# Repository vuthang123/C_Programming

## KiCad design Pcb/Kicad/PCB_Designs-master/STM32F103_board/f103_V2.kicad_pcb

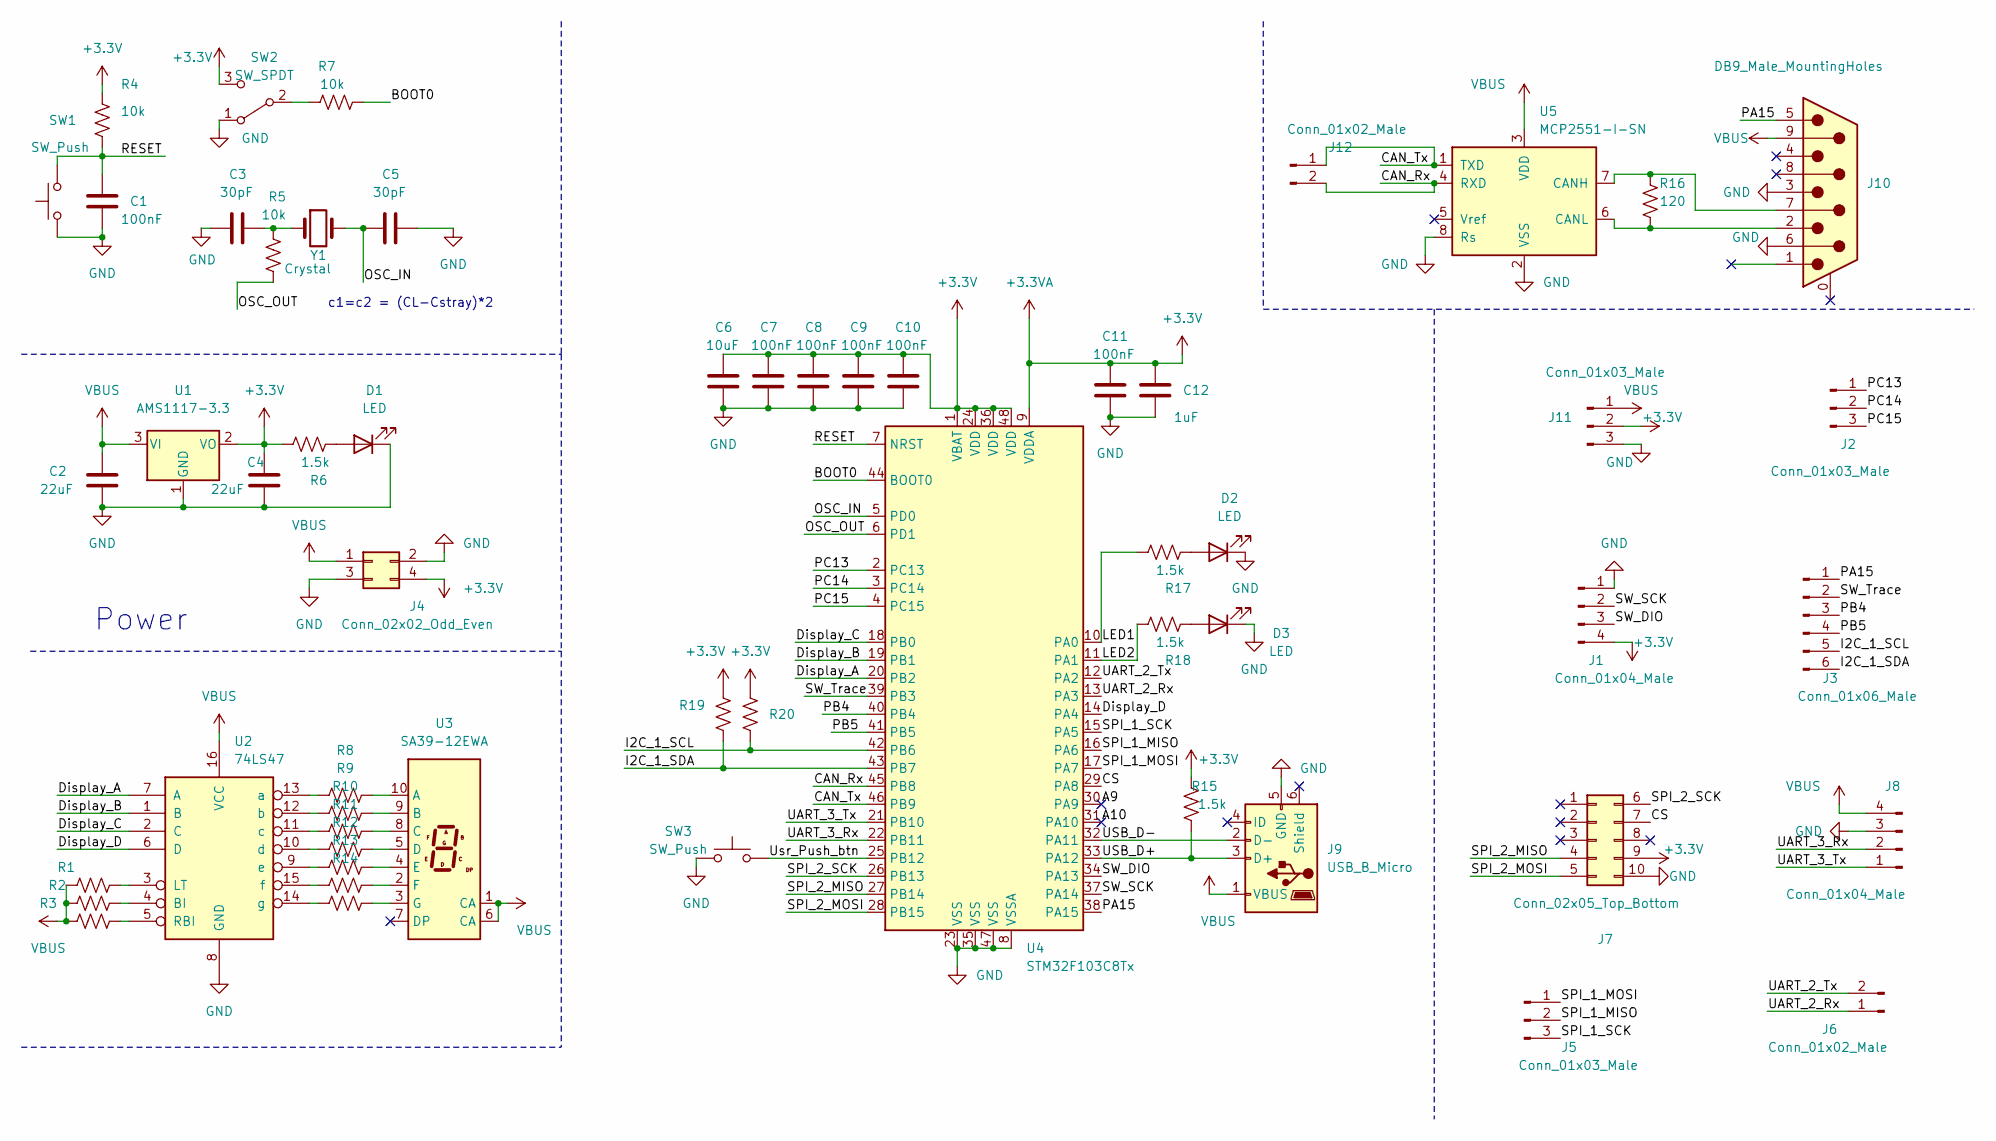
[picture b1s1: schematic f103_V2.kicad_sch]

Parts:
C1, C7, C8, C9, C10, C11: 100nF; C_0805_2012Metric_Pad1.18x1.45mm_HandSolder
C2, C4: 22uF; C_0805_2012Metric_Pad1.18x1.45mm_HandSolder
C3, C5: 30pF; C_0805_2012Metric_Pad1.18x1.45mm_HandSolder
C6: 10uF; C_0805_2012Metric_Pad1.18x1.45mm_HandSolder
C12: 1uF; C_0805_2012Metric_Pad1.18x1.45mm_HandSolder
D1, D2, D3: LED; LED_0805_2012Metric_Pad1.15x1.40mm_HandSolder
J1, J8: Conn_01x04_Male; PinHeader_1x04_P2.54mm_Vertical
J2, J5: Conn_01x03_Male; PinHeader_1x03_P2.54mm_Vertical
J3: Conn_01x06_Male; PinHeader_1x06_P2.54mm_Vertical
J4: Conn_02x02_Odd_Even; PinHeader_2x02_P2.54mm_Vertical
J6, J12: Conn_01x02_Male; PinHeader_1x02_P2.54mm_Vertical
J7: Conn_02x05_Top_Bottom; PinSocket_2x05_P2.54mm_Vertical
J9: USB_B_Micro; USB_Micro-B_Wuerth_629105150521
J10: DB9_Male_MountingHoles; DSUB-9_Male_Horizontal_P2.77x2.84mm_EdgePinOffset4.94mm_Hou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
J11: Conn_01x03_Male; PhoenixContact_MCV_1,5_3-G-3.81_1x03_P3.81mm_Vertical
R1, R2, R3, R8, R9, R10, R11, R12, R13, R14, R19, R20: R_US; R_0805_2012Metric_Pad1.20x1.40mm_HandSolder
R4, R5, R7: 10k; R_0805_2012Metric_Pad1.20x1.40mm_HandSolder
R6, R15, R17, R18: 1.5k; R_0805_2012Metric_Pad1.20x1.40mm_HandSolder
R16: 120; R_0805_2012Metric_Pad1.20x1.40mm_HandSolder
SW1, SW3: SW_Push; SW_PUSH_6mm_H5mm
SW2: SW_SPDT; SW_Push_1P2T_Vertical_E-Switch_800UDP8P1A1M6
U1: AMS1117-3.3; SOT-223-3_TabPin2
U2: 74LS47; DIP794W45P254L1930H508Q16
U3: SA39-12EWA; Sx39-1xxxxx
U4: STM32F103C8Tx; LQFP-48_7x7mm_P0.5mm
U5: MCP2551-I-SN; DIP-8_W7.62mm
Y1: Crystal; Crystal_HC49-U_Vertical

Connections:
+3.3V: C4.1, C6.1, C7.1, C8.1, C9.1, C10.1, C11.1, C12.1, J1.4, J4.4, J7.9, J11.2, R4.1, R6.2, R15.2, R19.2, R20.2, SW2.3 (C), U1.2 (VO), U4.1 (VBAT), U4.9 (VDDA), U4.24 (VDD), U4.36 (VDD), U4.48 (VDD)
/A9: U4.30 (PA9)
/A10: U4.31 (PA10)
/BOOT0: R7.2, U4.44 (BOOT0)
/CAN_Rx: J12.2, U4.45 (PB8), U5.4 (RXD)
/CAN_Tx: J12.1, U4.46 (PB9), U5.1 (TXD)
/CS: J7.7, U4.29 (PA8)
/Display_A: U2.7 (A), U4.20 (PB2)
/Display_B: U2.1 (B), U4.19 (PB1)
/Display_C: U2.2 (C), U4.18 (PB0)
/Display_D: U2.6 (D), U4.14 (PA4)
/I2C_1_SCL: J3.5, R20.1, U4.42 (PB6)
/I2C_1_SDA: J3.6, R19.1, U4.43 (PB7)
/LED1: R17.2, U4.10 (PA0)
/LED2: R18.2, U4.11 (PA1)
/OSC_IN: C5.2, U4.5 (PD0), Y1.2
/OSC_OUT: R5.1, U4.6 (PD1)
/PA15: J3.1, J10.5, U4.38 (PA15)
/PB4: J3.3, U4.40 (PB4)
/PB5: J3.4, U4.41 (PB5)
/PC13: J2.1, U4.2 (PC13)
/PC14: J2.2, U4.3 (PC14)
/PC15: J2.3, U4.4 (PC15)
/RESET: C1.1, R4.2, SW1.2, U4.7 (NRST)
/SPI_1_MISO: J5.2, U4.16 (PA6)
/SPI_1_MOSI: J5.1, U4.17 (PA7)
/SPI_1_SCK: J5.3, U4.15 (PA5)
/SPI_2_MISO: J7.4, U4.27 (PB14)
/SPI_2_MOSI: J7.5, U4.28 (PB15)
/SPI_2_SCK: J7.6, U4.26 (PB13)
/SW_DIO: J1.3, U4.34 (PA13)
/SW_SCK: J1.2, U4.37 (PA14)
/SW_Trace: J3.2, U4.39 (PB3)
/UART_2_Rx: J6.1, U4.13 (PA3)
/UART_2_Tx: J6.2, U4.12 (PA2)
/UART_3_Rx: J8.2, U4.22 (PB11)
/UART_3_Tx: J8.1, U4.21 (PB10)
/USB_D+: J9.3 (D+), R15.1, U4.33 (PA12)
/USB_D-: J9.2 (D-), U4.32 (PA11)
/Usr_Push_btn: SW3.2, U4.25 (PB12)
GND: C1.2, C2.2, C3.2, C4.2, C5.1, C6.2, C7.2, C8.2, C9.2, C10.2, C11.2, C12.2, D1.1 (K), D2.1 (K), D3.1 (K), J1.1, J4.2, J4.3, J7.10, J8.3, J9.5 (GND), J10.3, J10.6, J11.3, SW1.1, SW2.1 (A), SW3.1, U1.1 (GND), U2.8 (GND), U4.8 (VSSA), U4.23 (VSS), U4.35 (VSS), U4.47 (VSS), U5.2 (VSS), U5.8 (Rs)
unnamed: C3.1, R5.2, Y1.1
unnamed: D1.2 (A), R6.1
unnamed: D2.2 (A), R17.1
unnamed: D3.2 (A), R18.1
unnamed: R7.1, SW2.2 (B)
unnamed: R2.2, U2.4 (BI)
unnamed: R1.2, U2.3 (LT)
unnamed: R3.2, U2.5 (RBI)
unnamed: R8.1, U2.13 (a)
unnamed: R9.1, U2.12 (b)
unnamed: R10.1, U2.11 (c)
unnamed: R11.1, U2.10 (d)
unnamed: R12.1, U2.9 (e)
unnamed: R13.1, U2.15 (f)
unnamed: R14.1, U2.14 (g)
unnamed: R8.2, U3.10 (A)
unnamed: R9.2, U3.9 (B)
unnamed: R10.2, U3.8 (C)
unnamed: R11.2, U3.5 (D)
unnamed: R12.2, U3.4 (E)
unnamed: R13.2, U3.2 (F)
unnamed: R14.2, U3.3 (G)
unnamed: J10.7, R16.2, U5.7 (CANH)
unnamed: J10.2, R16.1, U5.6 (CANL)
VBUS: C2.1, J4.1, J8.4, J9.1 (VBUS), J10.9, J11.1, R1.1, R2.1, R3.1, U1.3 (VI), U2.16 (VCC), U3.1 (CA), U3.6 (CA), U5.3 (VDD)

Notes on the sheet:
Power
c1=c2 = (CL-Cstray)*2

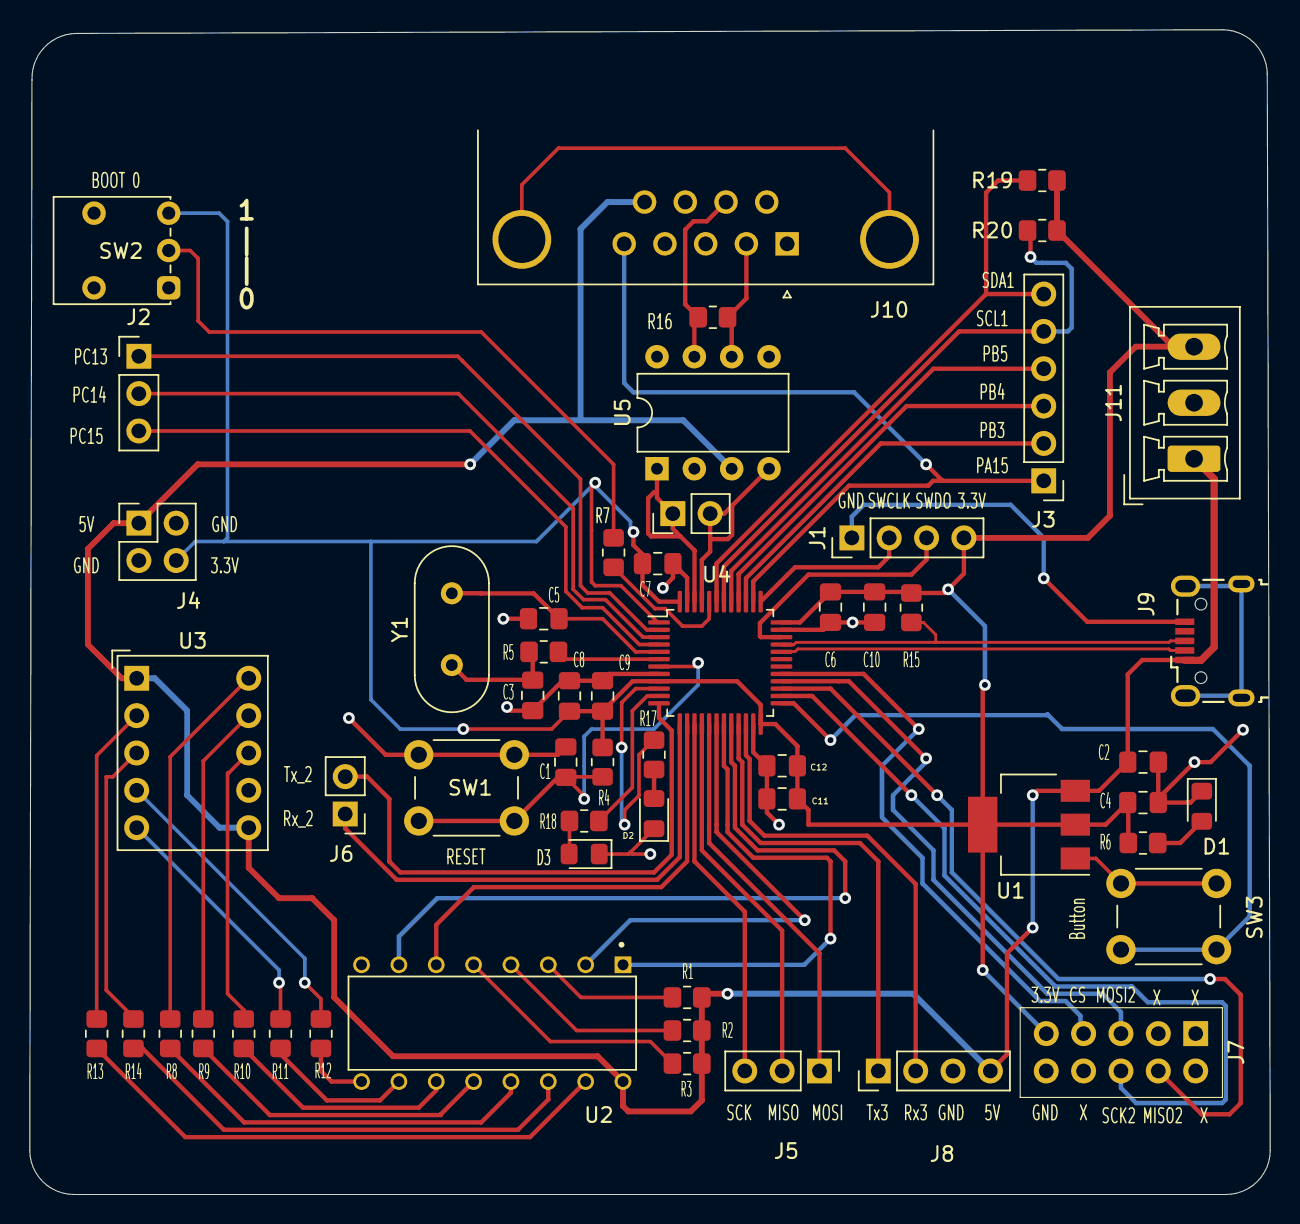
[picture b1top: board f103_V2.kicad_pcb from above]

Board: 2 copper layers, 84.4 x 79.2 mm, 56 parts (1 on the bottom side), 64 nets.

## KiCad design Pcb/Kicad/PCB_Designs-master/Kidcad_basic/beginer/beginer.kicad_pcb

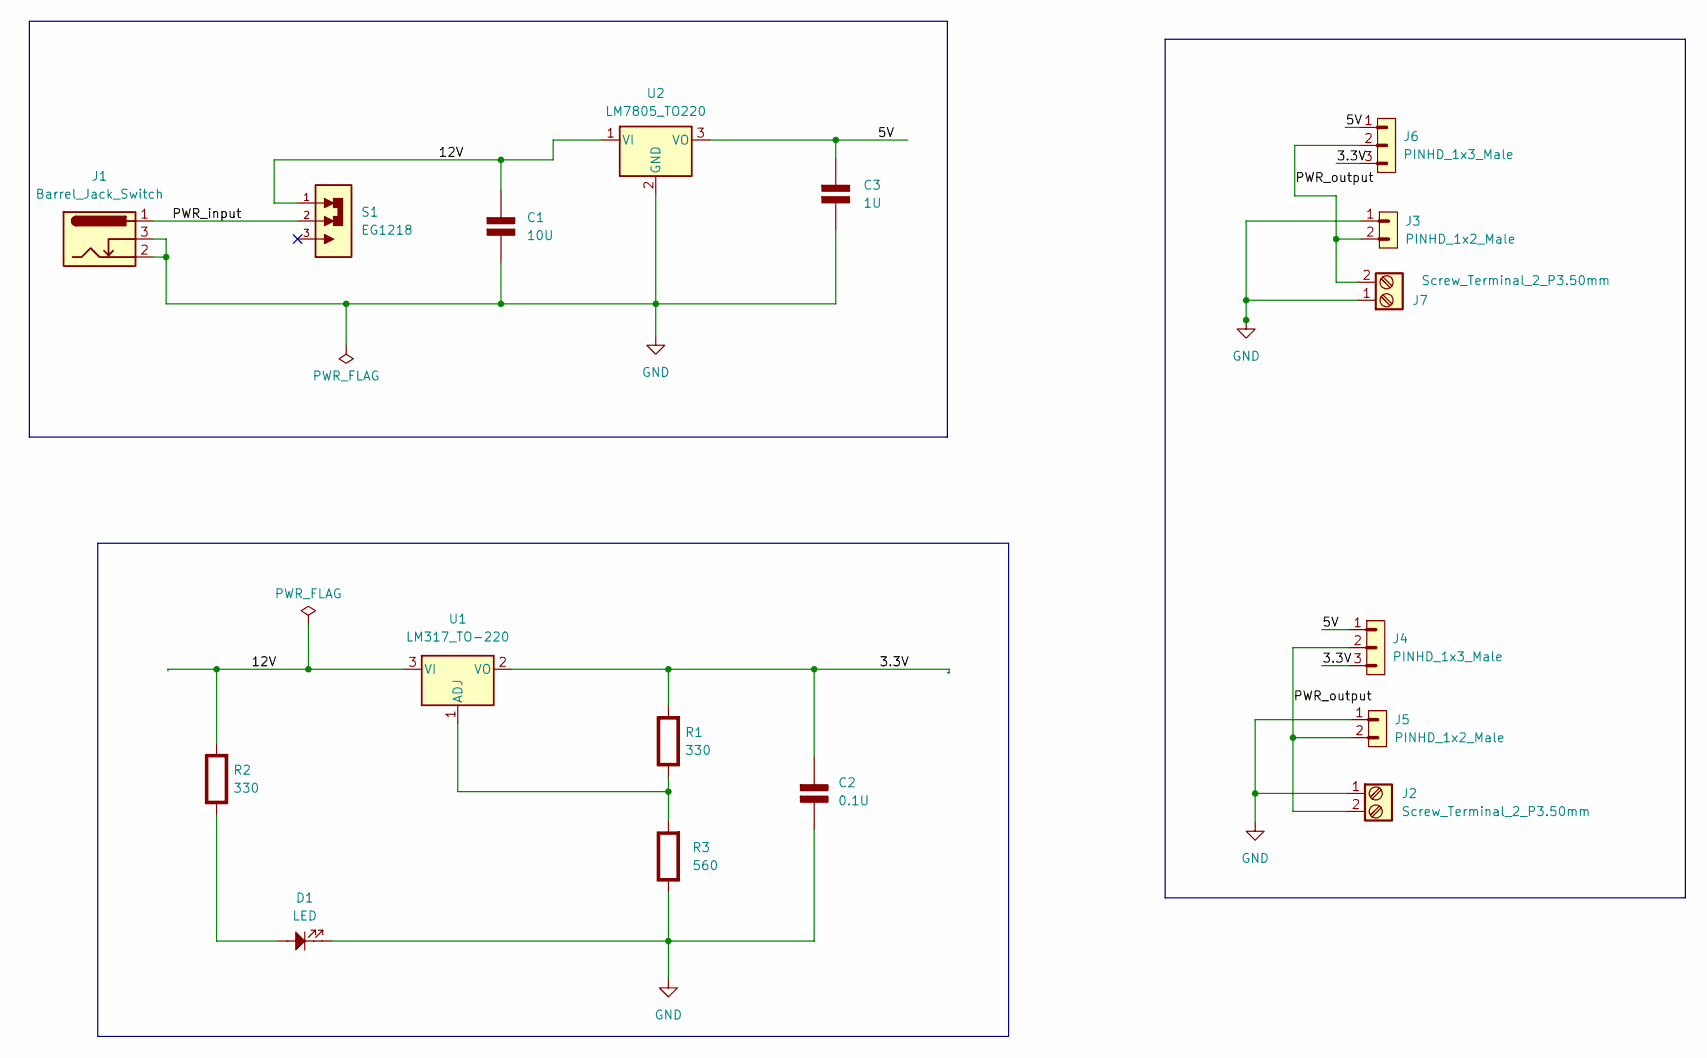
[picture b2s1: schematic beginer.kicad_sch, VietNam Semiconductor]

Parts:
C1: 10U; C_Disc_D3.0mm_W1.6mm_P2.50mm; Rating V
C2: 0.1U; C_Disc_D3.0mm_W1.6mm_P2.50mm; Rating V
C3: 1U; C_Disc_D3.0mm_W1.6mm_P2.50mm; Rating V
D1: LED; LED_D5.0mm
J1: Barrel_Jack_Switch; BarrelJack_Horizontal
J2, J7: Screw_Terminal_2_P3.50mm; TerminalBlock_Phoenix_PT-1,5-2-3.5-H_1x02_P3.50mm_Horizontal
J3, J5: PINHD_1x2_Male; PinHeader_1x02_P2.54mm_Vertical
J4, J6: PINHD_1x3_Male; PinHeader_1x03_P2.54mm_Vertical
R1, R2: 330; R_Axial_DIN0204_L3.6mm_D1.6mm_P7.62mm_Horizontal; Rating W
R3: 560; R_Axial_DIN0204_L3.6mm_D1.6mm_P7.62mm_Horizontal; Rating W
S1: EG1218; SW_EG1218
U1: LM317_TO-220; TO-220-3_Vertical
U2: LM7805_TO220; TO-220-3_Vertical

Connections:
/3.3V: C2.1 (+), J4.3, J6.3, R1.2 (-), U1.2 (VO)
/5V: C3.1 (+), J4.1, J6.1, U2.3 (VO)
/12V: C1.1 (+), R2.2 (-), S1.1, U1.3 (VI), U2.1 (VI)
/PWR_input: J1.1, S1.2
/PWR_output: J2.2, J3.2, J4.2, J5.2, J6.2, J7.2
GND: C1.2 (-), C2.2 (-), C3.2 (-), D1.1, J1.2, J1.3, J2.1, J3.1, J5.1, J7.1, R3.1 (+), U2.2 (GND)
unnamed: R1.1 (+), R3.2 (-), U1.1 (ADJ)
unnamed: D1.2, R2.1 (+)

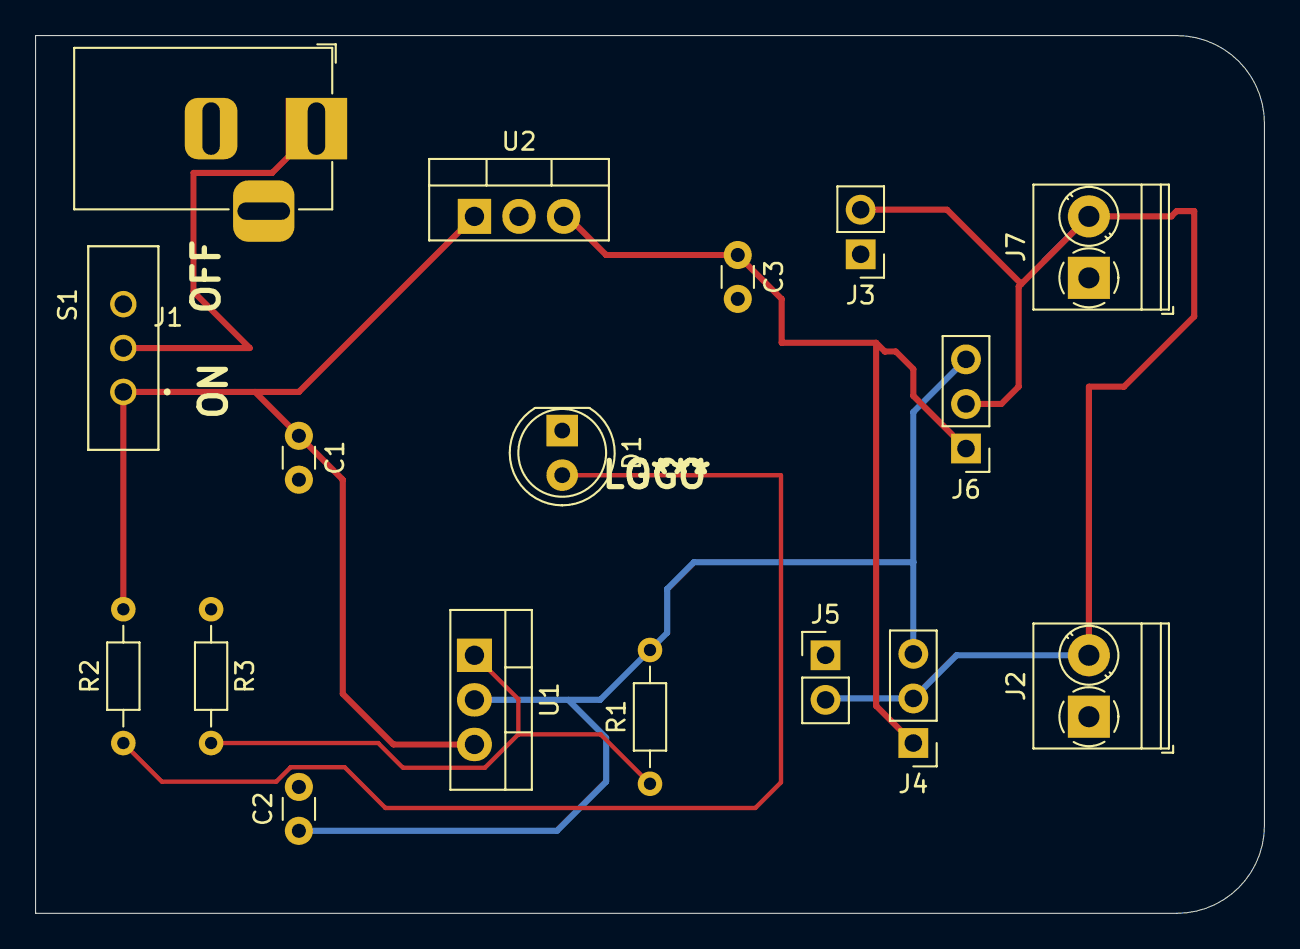
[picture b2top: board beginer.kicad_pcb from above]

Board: 2 copper layers, 70.0 x 50.0 mm, 17 parts (0 on the bottom side), 8 nets.

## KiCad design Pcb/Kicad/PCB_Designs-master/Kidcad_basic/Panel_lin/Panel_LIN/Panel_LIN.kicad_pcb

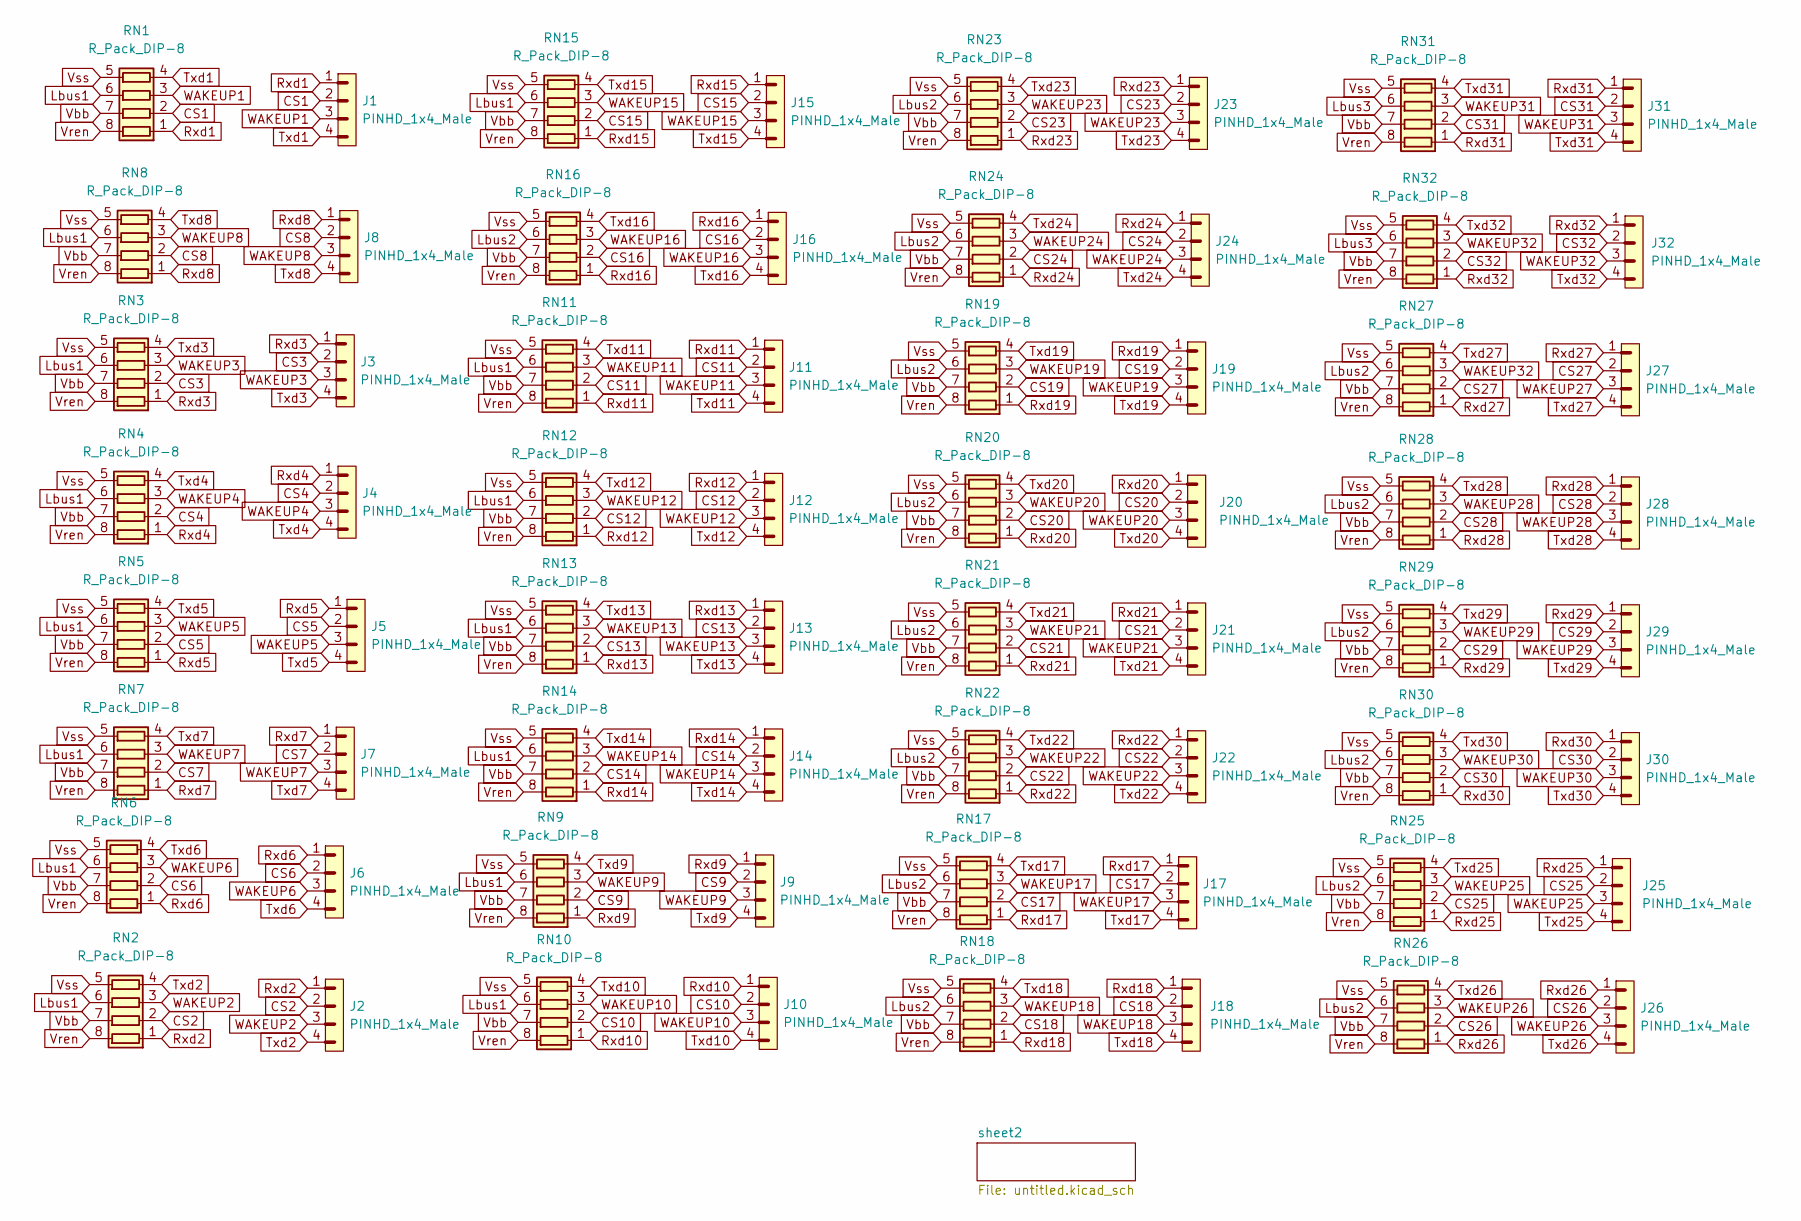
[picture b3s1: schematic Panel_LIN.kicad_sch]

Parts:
J1, J2, J3, J4, J5, J6, J7, J8, J9, J10, J11, J12, J13, J14, J15, J16, J17, J18, J19, J20, J21, J22, J23, J24, J25, J26, J27, J28, J29, J30, J31, J32: PINHD_1x4_Male; PinHeader_1x04_P2.54mm_Vertical
RN1, RN2, RN3, RN4, RN5, RN6, RN7, RN8, RN9, RN10, RN11, RN12, RN13, RN14, RN15, RN16, RN17, RN18, RN19, RN20, RN21, RN22, RN23, RN24, RN25, RN26, RN27, RN28, RN29, RN30, RN31, RN32: R_Pack_DIP-8; DIP-8_W7.62mm_LongPads

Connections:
CS1: J1.2, RN1.2 (R2.1)
CS2: J2.2, RN2.2 (R2.1)
CS3: J3.2, RN3.2 (R2.1)
CS4: J4.2, RN4.2 (R2.1)
CS5: J5.2, RN5.2 (R2.1)
CS6: J6.2, RN6.2 (R2.1)
CS7: J7.2, RN7.2 (R2.1)
CS8: J8.2, RN8.2 (R2.1)
CS9: J9.2, RN9.2 (R2.1)
CS10: J10.2, RN10.2 (R2.1)
CS11: J11.2, RN11.2 (R2.1)
CS12: J12.2, RN12.2 (R2.1)
CS13: J13.2, RN13.2 (R2.1)
CS14: J14.2, RN14.2 (R2.1)
CS15: J15.2, RN15.2 (R2.1)
CS16: J16.2, RN16.2 (R2.1)
CS17: J17.2, RN17.2 (R2.1)
CS18: J18.2, RN18.2 (R2.1)
CS19: J19.2, RN19.2 (R2.1)
CS20: J20.2, RN20.2 (R2.1)
CS21: J21.2, RN21.2 (R2.1)
CS22: J22.2, RN22.2 (R2.1)
CS23: J23.2, RN23.2 (R2.1)
CS24: J24.2, RN24.2 (R2.1)
CS25: J25.2, RN25.2 (R2.1)
CS26: J26.2, RN26.2 (R2.1)
CS27: J27.2, RN27.2 (R2.1)
CS28: J28.2, RN28.2 (R2.1)
CS29: J29.2, RN29.2 (R2.1)
CS30: J30.2, RN30.2 (R2.1)
CS31: J31.2, RN31.2 (R2.1)
CS32: J32.2, RN32.2 (R2.1)
Lbus1: RN1.6 (R3.2), RN2.6 (R3.2), RN3.6 (R3.2), RN4.6 (R3.2), RN5.6 (R3.2), RN6.6 (R3.2), RN7.6 (R3.2), RN8.6 (R3.2), RN9.6 (R3.2), RN10.6 (R3.2), RN11.6 (R3.2), RN12.6 (R3.2), RN13.6 (R3.2), RN14.6 (R3.2), RN15.6 (R3.2)
Lbus2: RN16.6 (R3.2), RN17.6 (R3.2), RN18.6 (R3.2), RN19.6 (R3.2), RN20.6 (R3.2), RN21.6 (R3.2), RN22.6 (R3.2), RN23.6 (R3.2), RN24.6 (R3.2), RN25.6 (R3.2), RN26.6 (R3.2), RN27.6 (R3.2), RN28.6 (R3.2), RN29.6 (R3.2), RN30.6 (R3.2)
Lbus3: RN31.6 (R3.2), RN32.6 (R3.2); also elsewhere on the board
Rxd1: J1.1, RN1.1 (R1.1)
Rxd2: J2.1, RN2.1 (R1.1)
Rxd3: J3.1, RN3.1 (R1.1)
Rxd4: J4.1, RN4.1 (R1.1)
Rxd5: J5.1, RN5.1 (R1.1)
Rxd6: J6.1, RN6.1 (R1.1)
Rxd7: J7.1, RN7.1 (R1.1)
Rxd8: J8.1, RN8.1 (R1.1)
Rxd9: J9.1, RN9.1 (R1.1)
Rxd10: J10.1, RN10.1 (R1.1)
Rxd11: J11.1, RN11.1 (R1.1)
Rxd12: J12.1, RN12.1 (R1.1)
Rxd13: J13.1, RN13.1 (R1.1)
Rxd14: J14.1, RN14.1 (R1.1)
Rxd15: J15.1, RN15.1 (R1.1)
Rxd16: J16.1, RN16.1 (R1.1)
Rxd17: J17.1, RN17.1 (R1.1)
Rxd18: J18.1, RN18.1 (R1.1)
Rxd19: J19.1, RN19.1 (R1.1)
Rxd20: J20.1, RN20.1 (R1.1)
Rxd21: J21.1, RN21.1 (R1.1)
Rxd22: J22.1, RN22.1 (R1.1)
Rxd23: J23.1, RN23.1 (R1.1)
Rxd24: J24.1, RN24.1 (R1.1)
Rxd25: J25.1, RN25.1 (R1.1)
Rxd26: J26.1, RN26.1 (R1.1)
Rxd27: J27.1, RN27.1 (R1.1)
Rxd28: J28.1, RN28.1 (R1.1)
Rxd29: J29.1, RN29.1 (R1.1)
Rxd30: J30.1, RN30.1 (R1.1)
Rxd31: J31.1, RN31.1 (R1.1)
Rxd32: J32.1, RN32.1 (R1.1)
Txd1: J1.4, RN1.4 (R4.1)
Txd2: J2.4, RN2.4 (R4.1)
Txd3: J3.4, RN3.4 (R4.1)
Txd4: J4.4, RN4.4 (R4.1)
Txd5: J5.4, RN5.4 (R4.1)
Txd6: J6.4, RN6.4 (R4.1)
Txd7: J7.4, RN7.4 (R4.1)
Txd8: J8.4, RN8.4 (R4.1)
Txd9: J9.4, RN9.4 (R4.1)
Txd10: J10.4, RN10.4 (R4.1)
Txd11: J11.4, RN11.4 (R4.1)
Txd12: J12.4, RN12.4 (R4.1)
Txd13: J13.4, RN13.4 (R4.1)
Txd14: J14.4, RN14.4 (R4.1)
Txd15: J15.4, RN15.4 (R4.1)
Txd16: J16.4, RN16.4 (R4.1)
Txd17: J17.4, RN17.4 (R4.1)
Txd18: J18.4, RN18.4 (R4.1)
Txd19: J19.4, RN19.4 (R4.1)
Txd20: J20.4, RN20.4 (R4.1)
Txd21: J21.4, RN21.4 (R4.1)
Txd22: J22.4, RN22.4 (R4.1)
Txd23: J23.4, RN23.4 (R4.1)
Txd24: J24.4, RN24.4 (R4.1)
Txd25: J25.4, RN25.4 (R4.1)
Txd26: J26.4, RN26.4 (R4.1)
Txd27: J27.4, RN27.4 (R4.1)
Txd28: J28.4, RN28.4 (R4.1)
Txd29: J29.4, RN29.4 (R4.1)
Txd30: J30.4, RN30.4 (R4.1)
Txd31: J31.4, RN31.4 (R4.1)
Txd32: J32.4, RN32.4 (R4.1)
Vbb: RN1.7 (R2.2), RN2.7 (R2.2), RN3.7 (R2.2), RN4.7 (R2.2), RN5.7 (R2.2), RN6.7 (R2.2), RN7.7 (R2.2), RN8.7 (R2.2), RN9.7 (R2.2), RN10.7 (R2.2), RN11.7 (R2.2), RN12.7 (R2.2), RN13.7 (R2.2), RN14.7 (R2.2), RN15.7 (R2.2), RN16.7 (R2.2), RN17.7 (R2.2), RN18.7 (R2.2), RN19.7 (R2.2), RN20.7 (R2.2), RN21.7 (R2.2), RN22.7 (R2.2), RN23.7 (R2.2), RN24.7 (R2.2), RN25.7 (R2.2), RN26.7 (R2.2), RN27.7 (R2.2), RN28.7 (R2.2), RN29.7 (R2.2), RN30.7 (R2.2), RN31.7 (R2.2), RN32.7 (R2.2); also elsewhere on the board
Vren: RN1.8 (R1.2), RN2.8 (R1.2), RN3.8 (R1.2), RN4.8 (R1.2), RN5.8 (R1.2), RN6.8 (R1.2), RN7.8 (R1.2), RN8.8 (R1.2), RN9.8 (R1.2), RN10.8 (R1.2), RN11.8 (R1.2), RN12.8 (R1.2), RN13.8 (R1.2), RN14.8 (R1.2), RN15.8 (R1.2), RN16.8 (R1.2), RN17.8 (R1.2), RN18.8 (R1.2), RN19.8 (R1.2), RN20.8 (R1.2), RN21.8 (R1.2), RN22.8 (R1.2), RN23.8 (R1.2), RN24.8 (R1.2), RN25.8 (R1.2), RN26.8 (R1.2), RN27.8 (R1.2), RN28.8 (R1.2), RN29.8 (R1.2), RN30.8 (R1.2), RN31.8 (R1.2), RN32.8 (R1.2); also elsewhere on the board
Vss: RN1.5 (R4.2), RN2.5 (R4.2), RN3.5 (R4.2), RN4.5 (R4.2), RN5.5 (R4.2), RN6.5 (R4.2), RN7.5 (R4.2), RN8.5 (R4.2), RN9.5 (R4.2), RN10.5 (R4.2), RN11.5 (R4.2), RN12.5 (R4.2), RN13.5 (R4.2), RN14.5 (R4.2), RN15.5 (R4.2), RN16.5 (R4.2), RN17.5 (R4.2), RN18.5 (R4.2), RN19.5 (R4.2), RN20.5 (R4.2), RN21.5 (R4.2), RN22.5 (R4.2), RN23.5 (R4.2), RN24.5 (R4.2), RN25.5 (R4.2), RN26.5 (R4.2), RN27.5 (R4.2), RN28.5 (R4.2), RN29.5 (R4.2), RN30.5 (R4.2), RN31.5 (R4.2), RN32.5 (R4.2); also elsewhere on the board
WAKEUP1: J1.3, RN1.3 (R3.1)
WAKEUP2: J2.3, RN2.3 (R3.1)
WAKEUP3: J3.3, RN3.3 (R3.1)
WAKEUP4: J4.3, RN4.3 (R3.1)
WAKEUP5: J5.3, RN5.3 (R3.1)
WAKEUP6: J6.3, RN6.3 (R3.1)
WAKEUP7: J7.3, RN7.3 (R3.1)
WAKEUP8: J8.3, RN8.3 (R3.1)
WAKEUP9: J9.3, RN9.3 (R3.1)
WAKEUP10: J10.3, RN10.3 (R3.1)
WAKEUP11: J11.3, RN11.3 (R3.1)
WAKEUP12: J12.3, RN12.3 (R3.1)
WAKEUP13: J13.3, RN13.3 (R3.1)
WAKEUP14: J14.3, RN14.3 (R3.1)
WAKEUP15: J15.3, RN15.3 (R3.1)
WAKEUP16: J16.3, RN16.3 (R3.1)
WAKEUP17: J17.3, RN17.3 (R3.1)
WAKEUP18: J18.3, RN18.3 (R3.1)
WAKEUP19: J19.3, RN19.3 (R3.1)
WAKEUP20: J20.3, RN20.3 (R3.1)
WAKEUP21: J21.3, RN21.3 (R3.1)
WAKEUP22: J22.3, RN22.3 (R3.1)
WAKEUP23: J23.3, RN23.3 (R3.1)
WAKEUP24: J24.3, RN24.3 (R3.1)
WAKEUP25: J25.3, RN25.3 (R3.1)
WAKEUP26: J26.3, RN26.3 (R3.1)
WAKEUP28: J28.3, RN28.3 (R3.1)
WAKEUP29: J29.3, RN29.3 (R3.1)
WAKEUP30: J30.3, RN30.3 (R3.1)
WAKEUP31: J31.3, RN31.3 (R3.1)

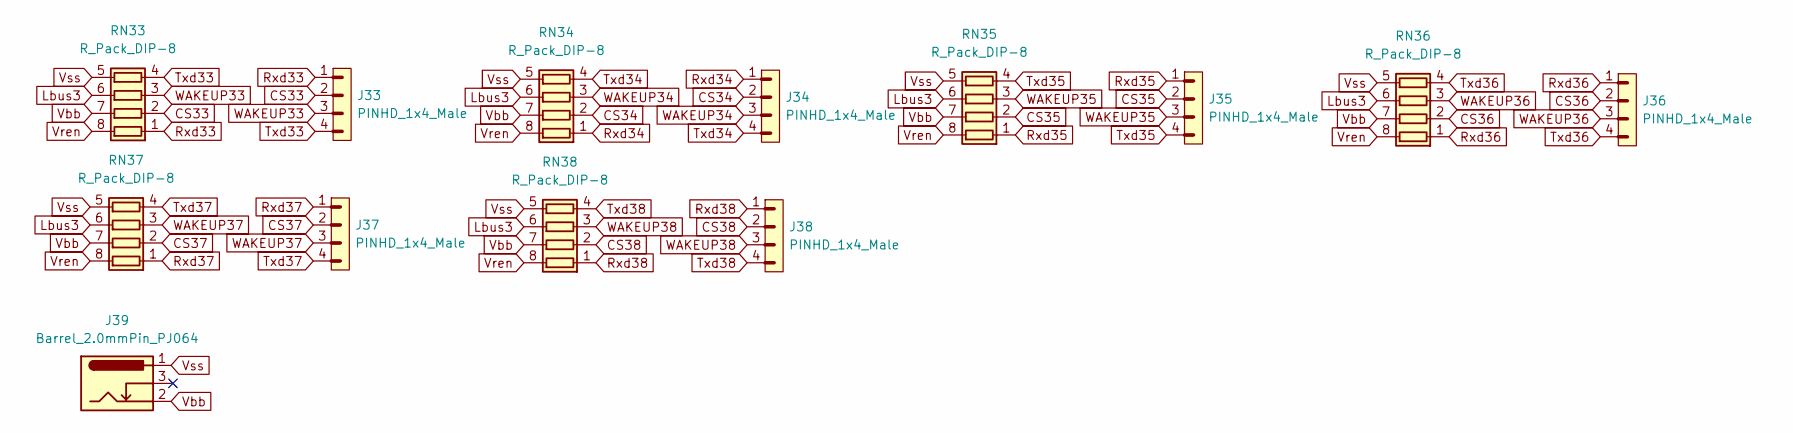
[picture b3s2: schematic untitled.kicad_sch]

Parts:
J33, J34, J35, J36, J37, J38: PINHD_1x4_Male; PinHeader_1x04_P2.54mm_Vertical
J39: Barrel_2.0mmPin_PJ064; BarrelJack_Horizontal; Part Number WQP-DC026M (2.0mm center pin)
RN33, RN34, RN35, RN36, RN37, RN38: R_Pack_DIP-8; DIP-8_W7.62mm_LongPads

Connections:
CS33: J33.2, RN33.2 (R2.1)
CS34: J34.2, RN34.2 (R2.1)
CS35: J35.2, RN35.2 (R2.1)
CS36: J36.2, RN36.2 (R2.1)
CS37: J37.2, RN37.2 (R2.1)
CS38: J38.2, RN38.2 (R2.1)
Lbus3: RN33.6 (R3.2), RN34.6 (R3.2), RN35.6 (R3.2), RN36.6 (R3.2), RN37.6 (R3.2), RN38.6 (R3.2); also elsewhere on the board
Rxd33: J33.1, RN33.1 (R1.1)
Rxd34: J34.1, RN34.1 (R1.1)
Rxd35: J35.1, RN35.1 (R1.1)
Rxd36: J36.1, RN36.1 (R1.1)
Rxd37: J37.1, RN37.1 (R1.1)
Rxd38: J38.1, RN38.1 (R1.1)
Txd33: J33.4, RN33.4 (R4.1)
Txd34: J34.4, RN34.4 (R4.1)
Txd35: J35.4, RN35.4 (R4.1)
Txd36: J36.4, RN36.4 (R4.1)
Txd37: J37.4, RN37.4 (R4.1)
Txd38: J38.4, RN38.4 (R4.1)
Vbb: J39.2, RN33.7 (R2.2), RN34.7 (R2.2), RN35.7 (R2.2), RN36.7 (R2.2), RN37.7 (R2.2), RN38.7 (R2.2); also elsewhere on the board
Vren: RN33.8 (R1.2), RN34.8 (R1.2), RN35.8 (R1.2), RN36.8 (R1.2), RN37.8 (R1.2), RN38.8 (R1.2); also elsewhere on the board
Vss: J39.1, RN33.5 (R4.2), RN34.5 (R4.2), RN35.5 (R4.2), RN36.5 (R4.2), RN37.5 (R4.2), RN38.5 (R4.2); also elsewhere on the board
WAKEUP33: J33.3, RN33.3 (R3.1)
WAKEUP34: J34.3, RN34.3 (R3.1)
WAKEUP35: J35.3, RN35.3 (R3.1)
WAKEUP36: J36.3, RN36.3 (R3.1)
WAKEUP37: J37.3, RN37.3 (R3.1)
WAKEUP38: J38.3, RN38.3 (R3.1)

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
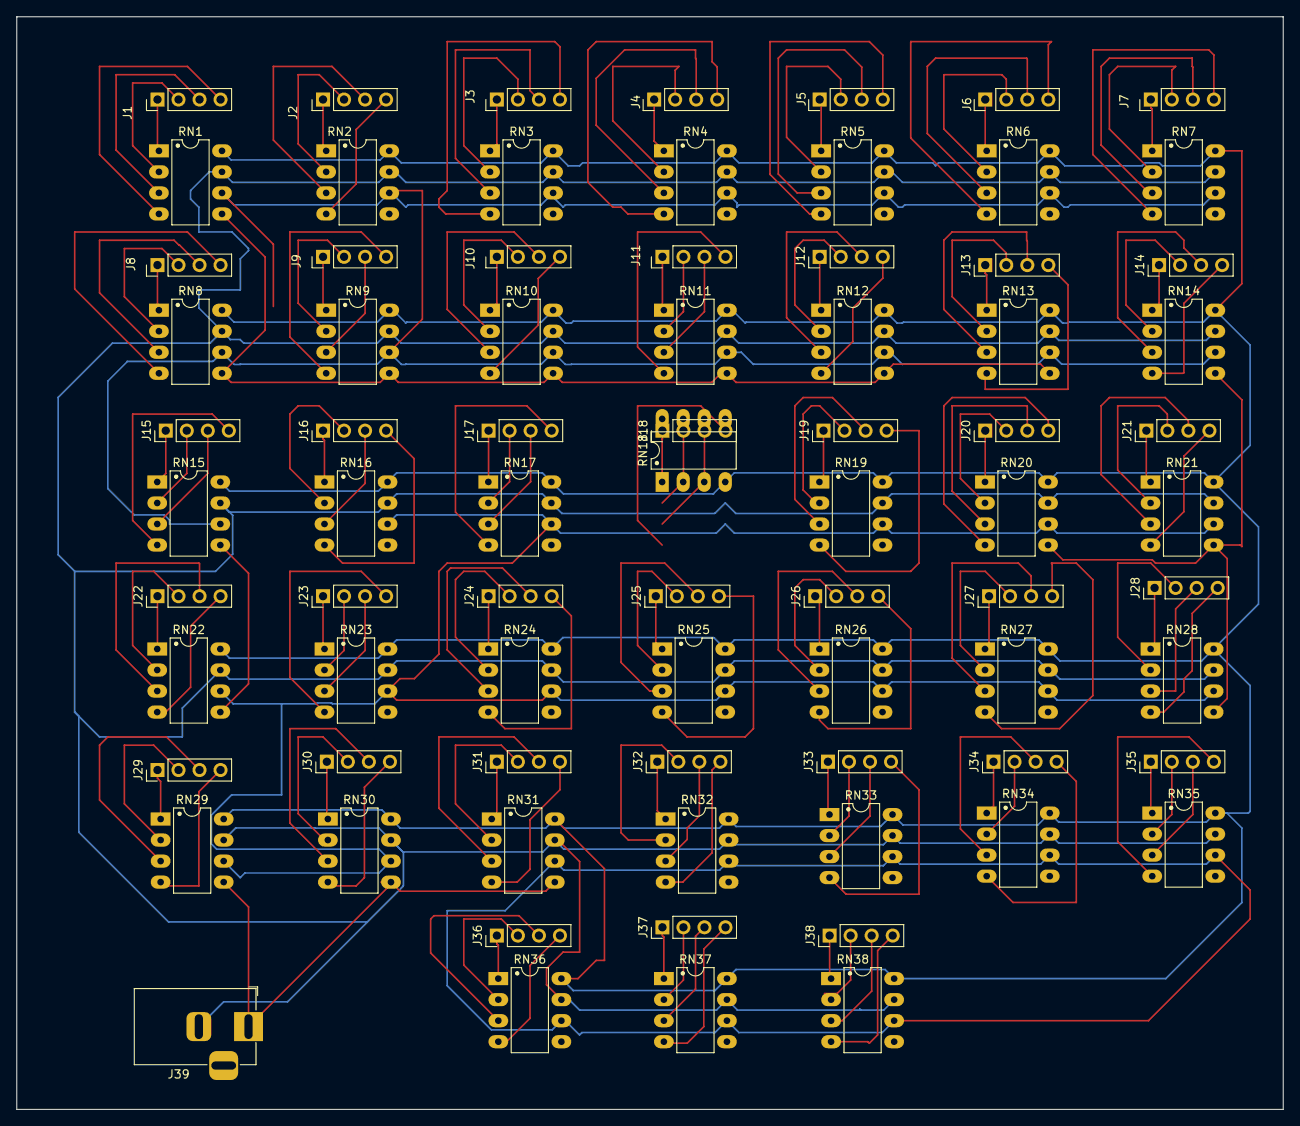
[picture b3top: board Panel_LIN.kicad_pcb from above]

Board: 2 copper layers, 153.0 x 132.0 mm, 77 parts (0 on the bottom side), 158 nets.

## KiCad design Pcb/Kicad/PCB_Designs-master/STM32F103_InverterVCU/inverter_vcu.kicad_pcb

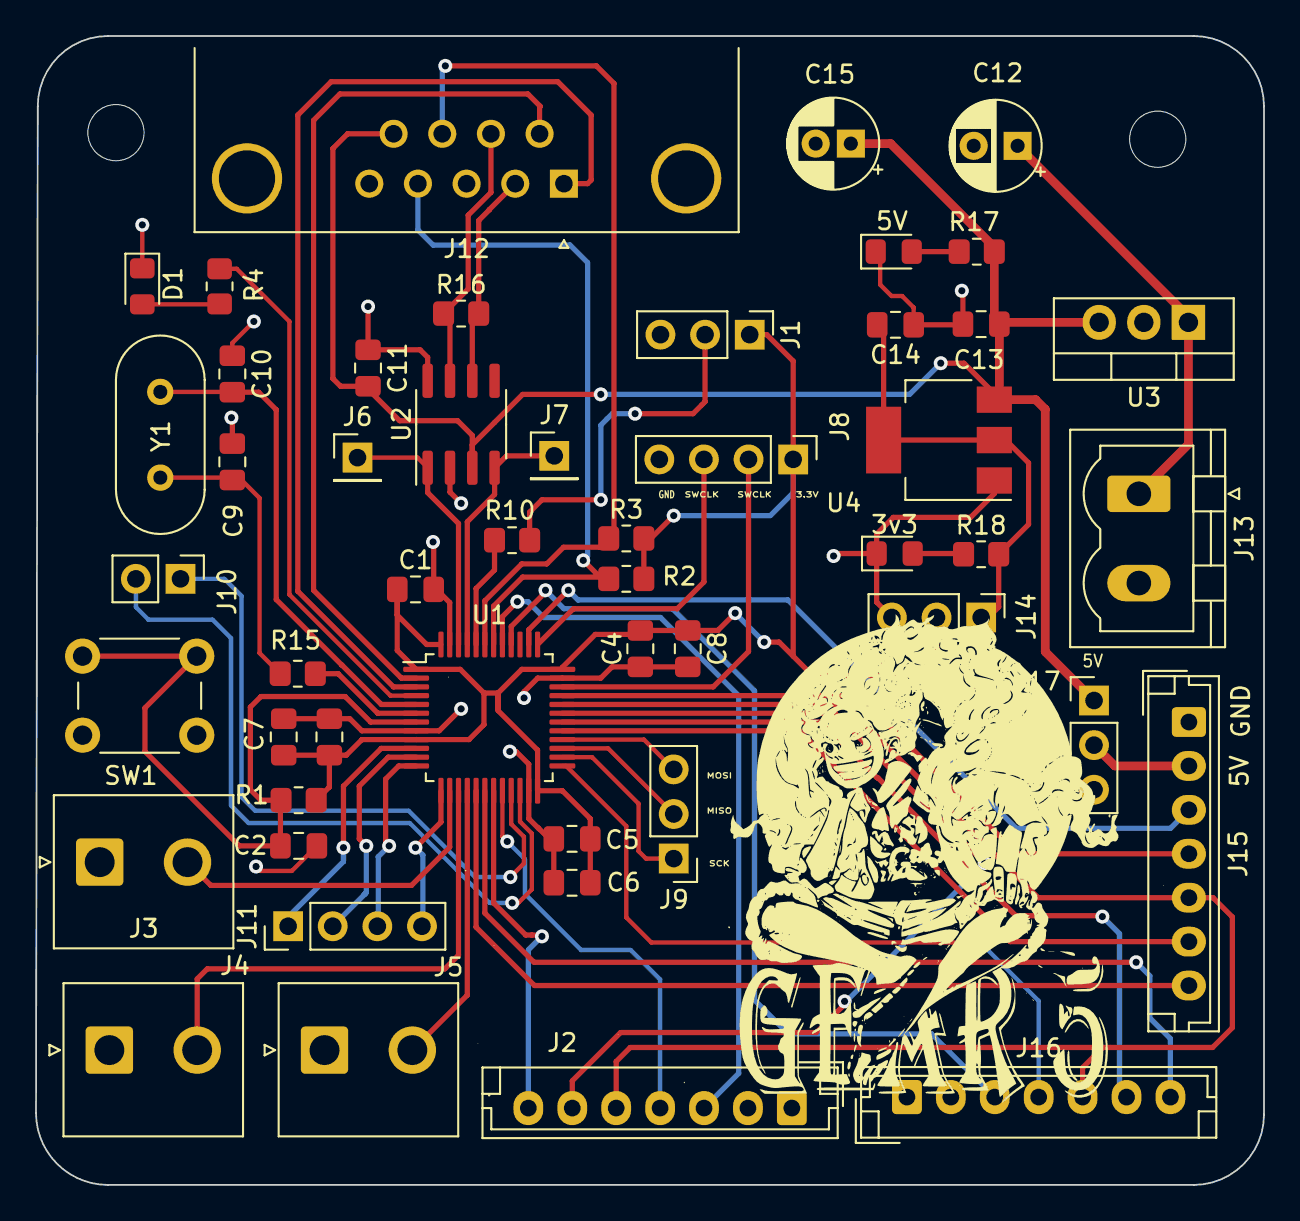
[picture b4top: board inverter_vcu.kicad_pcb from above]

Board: 2 copper layers, 69.9 x 65.4 mm, 50 parts (0 on the bottom side), 51 nets.

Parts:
3v3, 5V: LED; LED_0805_2012Metric_Pad1.15x1.40mm_HandSolder
C1, C11: 10uF; C_0805_2012Metric_Pad1.18x1.45mm_HandSolder
C2, C3, C4, C5, C6, C7: 100nF; C_0805_2012Metric_Pad1.18x1.45mm_HandSolder
C8: 1uF; C_0805_2012Metric_Pad1.18x1.45mm_HandSolder
C9, C10: 30pF; C_0805_2012Metric_Pad1.18x1.45mm_HandSolder
C12: 22uF; CP_Radial_D5.0mm_P2.50mm
C13, C14: 22uF; C_0805_2012Metric_Pad1.18x1.45mm_HandSolder
C15: 22uF; CP_Radial_D5.0mm_P2.00mm
D1: LED; LED_0805_2012Metric_Pad1.15x1.40mm_HandSolder
J1, J9, J14, J17: Conn_01x03_Male; PinHeader_1x03_P2.54mm_Vertical
J2, J15, J16: Conn_01x07_Male; JST_EH_B7B-EH-A_1x07_P2.50mm_Vertical
J3, J4, J5: Conn_01x02_Male; JST_NV_B02P-NV_1x02_P5.00mm_Vertical
J6, J7: Conn_01x01_Male; PinHeader_1x01_P2.54mm_Vertical
J8, J11: Conn_01x04_Male; PinHeader_1x04_P2.54mm_Vertical
J10: Conn_01x02_Male; PinHeader_1x02_P2.54mm_Vertical
J12: DB9_Male_MountingHoles; DSUB-9_Male_Horizontal_P2.77x2.84mm_EdgePinOffset4.94mm_Hou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
J13: Conn_01x02_Male; PhoenixContact_MSTBVA_2,5_2-G-5,08_1x02_P5.08mm_Vertical
R1, R10, R15: 10k; R_0805_2012Metric_Pad1.20x1.40mm_HandSolder
R2, R3, R4, R16, R17, R18: 1.5k; R_0805_2012Metric_Pad1.20x1.40mm_HandSolder
SW1: SW_Push; SW_PUSH_6mm_H5mm
U1: STM32F103C8Tx; LQFP-48_7x7mm_P0.5mm
U2: MCP2551-I-SN; SOIC-8_3.9x4.9mm_P1.27mm
U3: LM7805_TO220; TO-220-3_Vertical
U4: AMS1117-3.3; SOT-223-3_TabPin2
Y1: Crystal; Crystal_HC49-U_Vertical

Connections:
+3.3V: C1.1, C3.1, C4.1, C5.1, C6.1, C7.1, C8.1, J1.1, J8.1, J14.2, R1.1, R2.2, R3.2, U1.1 (VBAT), U1.9 (VDDA), U1.24 (VDD), U1.36 (VDD), U1.48 (VDD)
+5V: C11.2, C13.1, C15.1, J12.9, J17.1, R17.2, U2.3 (VDD), U3.3 (VO), U4.3 (VI)
+BATT: C12.1, J13.1, U3.1 (VI)
/BOOT0: R10.2, U1.44 (BOOT0)
/CAN_H+: J12.7, R16.1, U2.7 (CANH)
/CAN_L-: J12.2, R16.2, U2.6 (CANL)
/CAN_Rx: J7.1, U1.45 (PB8), U2.4 (RXD)
/CAN_Tx: J6.1, U1.46 (PB9), U2.1 (TXD)
/I2C_SCL: J12.4, R2.1, U1.42 (PB6)
/I2C_SDA: J12.8, R3.1, U1.43 (PB7)
/MVCU_HBT: J12.1, U1.3 (PC14)
/OSC_IN: C10.2, U1.5 (PD0), Y1.2
/OSC_OUT: R15.1, U1.6 (PD1)
/RESET: C2.1, R1.2, SW1.2, U1.7 (NRST)
/SWCLK: J8.3, U1.37 (PA14)
/SWDIO: J8.2, U1.34 (PA13)
/VCU_HBT: J12.6, U1.2 (PC13)
/a7: J15.7, U1.17 (PA7)
/a8: J15.6, U1.29 (PA8)
/a9: J16.6, U1.30 (PA9)
/a10: J2.6, U1.31 (PA10)
/a11: J2.5, J15.5, J16.5, U1.32 (PA11)
/a12: J15.4, U1.33 (PA12)
/a15: J15.3, U1.38 (PA15)
/adc1: J3.2, U1.14 (PA4)
/adc2: J4.2, U1.15 (PA5)
/adc3: J5.2, U1.16 (PA6)
/b0: J16.7, U1.18 (PB0)
/b1: J2.7, U1.19 (PB1)
/fault1: J16.3, U1.40 (PB4)
/fault2: J2.3, U1.41 (PB5)
/miso: J9.2, U1.27 (PB14)
/mosi: J9.3, U1.28 (PB15)
/pmw_a2: J11.3, U1.12 (PA2)
/pwm_a0: J11.1, U1.10 (PA0)
/pwm_a1: J11.2, U1.11 (PA1)
/pwm_a3: J11.4, U1.13 (PA3)
/rdy1: J16.4, U1.25 (PB12)
/rdy2: J2.4, U1.20 (PB2)
/sck: J9.1, U1.26 (PB13)
/uart3_rx: J10.2, U1.22 (PB11)
/uart3_tx: J10.1, U1.21 (PB10)
GND: 3v3.1 (K), 5V.1 (K), C1.2, C2.2, C3.2, C4.2, C5.2, C6.2, C7.2, C8.2, C9.2, C10.1, C11.1, C12.2, C13.2, C14.2, C15.2, D1.1 (K), J1.3, J2.1, J3.1, J4.1, J5.1, J8.4, J12.0 (PAD), J12.3, J12.5, J13.2, J14.3, J15.1, J16.1, SW1.1, U1.8 (VSSA), U1.23 (VSS), U1.35 (VSS), U1.47 (VSS), U2.2 (VSS), U2.8 (Rs), U3.2 (GND), U4.1 (GND)
unnamed: C9.1, R15.2, Y1.1
unnamed: C14.1, J14.1, R18.2, U4.2 (VO)
unnamed: D1.2 (A), R4.1
unnamed: 5V.2 (A), R17.1
unnamed: 3v3.2 (A), R18.1
unnamed: J1.2, R10.1
unnamed: J15.2, J17.2
unnamed: R4.2, U1.4 (PC15)
